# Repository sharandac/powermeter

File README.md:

<p align="center">

&nbsp;

&nbsp;

</p>
<hr/>

# powermeter

A not so simple but very flexible smart meter based on ESP32. It supports MQTT, live monitoring via web interface, IO ports ( can be switched depending on measured values ), a simple OLED driver for simple value reports, editable opcode sequences per channel and group management. And the best is: everything can also be set via the web interface and has immediate effect and invites to play to improve the understanding of AC voltage/current or DC voltage/current.<br>
<h3 style="color:#00ff00">Note: From version 2022110101 a complete reconfiguration is required.</h3>
<h3 style="color:#ff0000">Danger: Working with 110V or 230V is dangerous!</h3>

# install

Clone this repository and open it with platformIO. Remember, the SPIFF must also be flashed. On a terminal in vscode you can do it with
```bash
pio run -t uploadfs
pio run -t upload
```

After that, take a look at your monitorport ...

```text
Read config from SPIFFS
scan for SSID "" ... not found
starting Wifi-AP with SSID "powermeter_aadee0"
AP IP address: 192.168.4.1
Start Main Task on Core: 1
Start NTP Task on Core: 1
Start Measurement Task on Core: 0
Start MQTT-Client on Core: 1
Start Webserver on Core: 1
NTP-client: renew time
Start OTA Task on Core: 1
Failed to obtain time
NTP-client: Thursday, January 01 1970 01:00:07
```
When the output look like this, congratulation!

After the first start an access point will be opened with an unique name like
```bash
powermeter_XXXXX
```
and an not so unique password
```bash
powermeter
```
After that you can configure the powermeter under the following IP-address with your favorite webbrowser
```bash
http://192.168.4.1 or powermeter_xxxxxx.local
```
# how it works

At any time, all 6 adc channel are read in simultaneously regardless of the settings. Afterwards, these 6 ADC channels are distributed to 13 virtual channels with the help of editable microopcodes, each sample has a maximum of 10 opcodes available for real-time calculations (mixing, sum calculation, reactive power and so on). These 13 virtual channels can then be combined into a maximum of 6 output groups. For more information about how AC current or three-phase current and power calculations works, [read here](https://en.wikipedia.org/wiki/Alternating_current) and [here](https://en.wikipedia.org/wiki/Three-phase_electric_power)

# sensor hardware

## Sensors
SCT013-000 current sensor (~100A)<br>

ZMPT101B voltage sensor (~250V)<br>

ACS712 current sensor 5A, 20A and 30A<br>

simple voltage divider<br>

For ratio calculation see inline documentation via webinterface.

## Display hardware
Uncomment in "**display.cpp**" the line of the display you want to use<br>
```c
//#include <Adafruit_SSD1306.h>
//#include  <Adafruit_SH110X.h>
```

# Interface

## live view

## round trip

# contributors

Every Contribution to this repository is highly welcome! Don't fear to create pull requests which enhance or fix the project, you are going to help everybody.
<p>
If you want to donate to the author then you can buy me a coffee.
<br/><br/>

</p>

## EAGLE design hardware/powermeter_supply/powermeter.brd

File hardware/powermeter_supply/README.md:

# powermeter with supply

Here is the simplest standalone powermeter with supply you can build with current and voltage measurement.

## eagle files

[schematic](powermeter.sch)<br>
[board](powermeter.brd)

## bill of material

1 x 150x100x1mm 35µm FR4 [amazon](https://amzn.eu/d/hufknsN)<br>
esp32 D1 mini [amazon](https://amzn.eu/d/gZaocqF)<br>
ZMPT101 [amazon](https://amzn.eu/d/3shv3Ax)<br>
SCT-013-000 [amazon](https://amzn.eu/d/5wpwDs4)<br>
AC-05-03 ( 110-250V/AC -> 5V/DC ) [amazon](https://amzn.eu/d/ckoURve)<br>
3.5mm jack [amazon](https://amzn.eu/d/a7YUG0G)<br>
MSTBA2 connector [amazon](https://amzn.eu/d/0bCERTn)<br>
2 x 10k resistor<br>
1 x 62R resistor<br>
1 x 1M resistor<br>
1 x 2M resistor<br>
1 x 47µF cap<br>

## gcode

The G-code files are intended for Chilipeppr with a CNC3018 and contain everything. Engraving, drilling and cutting. There are two files. A normal one, where you should have your own gcode for tool change and length measurement and one with the appropriate gcode that also contains the length measurement. The reference point is X=0 and Y=0.

A backlash-free Z-axis is very important for accurate engraving of the tracks and cutting out!

The following tools are required:

0.1mm milling bit<br>
0.6mm drill bit<br>
0.9mm drill bit<br>
1.2mm drill bit<br>
1.3mm drill bit<br>
1.4mm drill bit<br>
2.0mm end mill<br>

Drag and drop the preferred gcode file into Chilipeppr. Autoleveling is a must. And then just press play. For the tool change, the program is paused at the appropriate position (M6).

If everything has gone well, you are rewarded with a finished board without any post-processing and is ready to soldering.

## config

After soldering and software installtion (wifi,mqtt and so on) you can copy the content from config/measure.json to your powermeter. From here you can tweake the ratio settings for precise measuring via web interface under "channel settings".

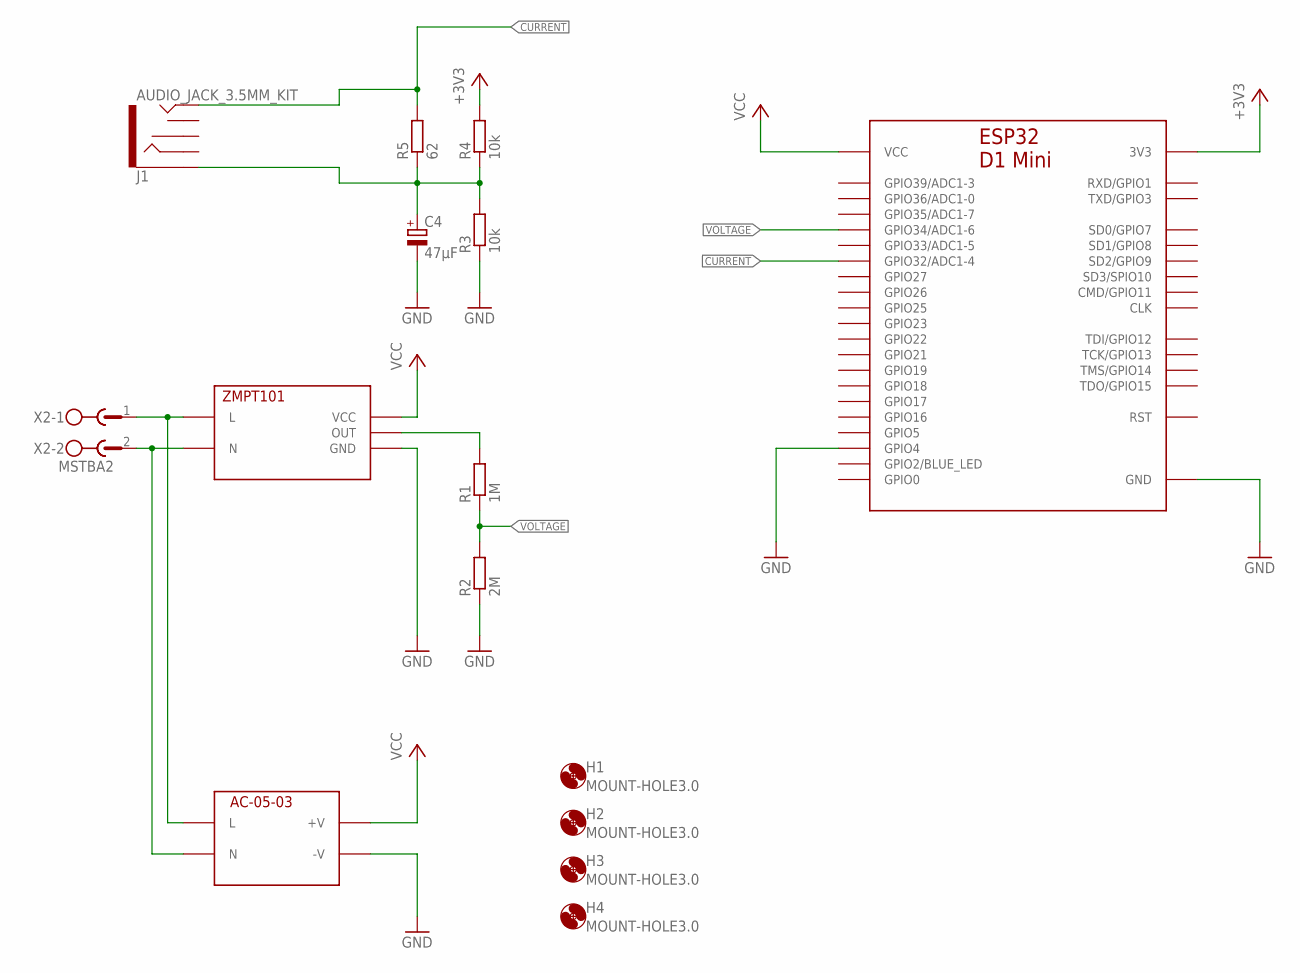
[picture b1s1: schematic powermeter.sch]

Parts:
C4: 47µF; E2,5-5
H1, H2, H3, H4: MOUNT-HOLE3.0; 3,0
J1: AUDIO_JACK_3.5MM_KIT; AUDIO-JACK-KIT
R1: 1M; 0204/7
R2: 2M; 0204/7
R3, R4: 10k; 0204/7
R5: 62; 0204/7
U1: ESP32D1MINI
U$1: ZMPT101
U$2: AC-05-03
X2: MSTBA2

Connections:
+3V3: R4.2, U1.3V3
CURRENT: J1.TIP, R5.2, U1.IO32 (GPIO32/ADC1-4)
GND: C4.-, R2.1, R3.1, U1.GND1 (GND), U1.GND2 (GND), U1.GND3 (GND), U1.IO4 (GPIO4), U$1.P$3 (GND), U$1.P$4 (GND), U$2.-V
unnamed: R1.2, U$1.OUT
unnamed: U$1.L, U$2.L, X2.1
unnamed: C4.+, J1.SLEEVE, R3.2, R4.1, R5.1
unnamed: U$1.N, U$2.N, X2.2
VCC: U1.VCC, U$1.VCC, U$2.+V
VOLTAGE: R1.1, R2.2, U1.IO34 (GPIO34/ADC1-6)

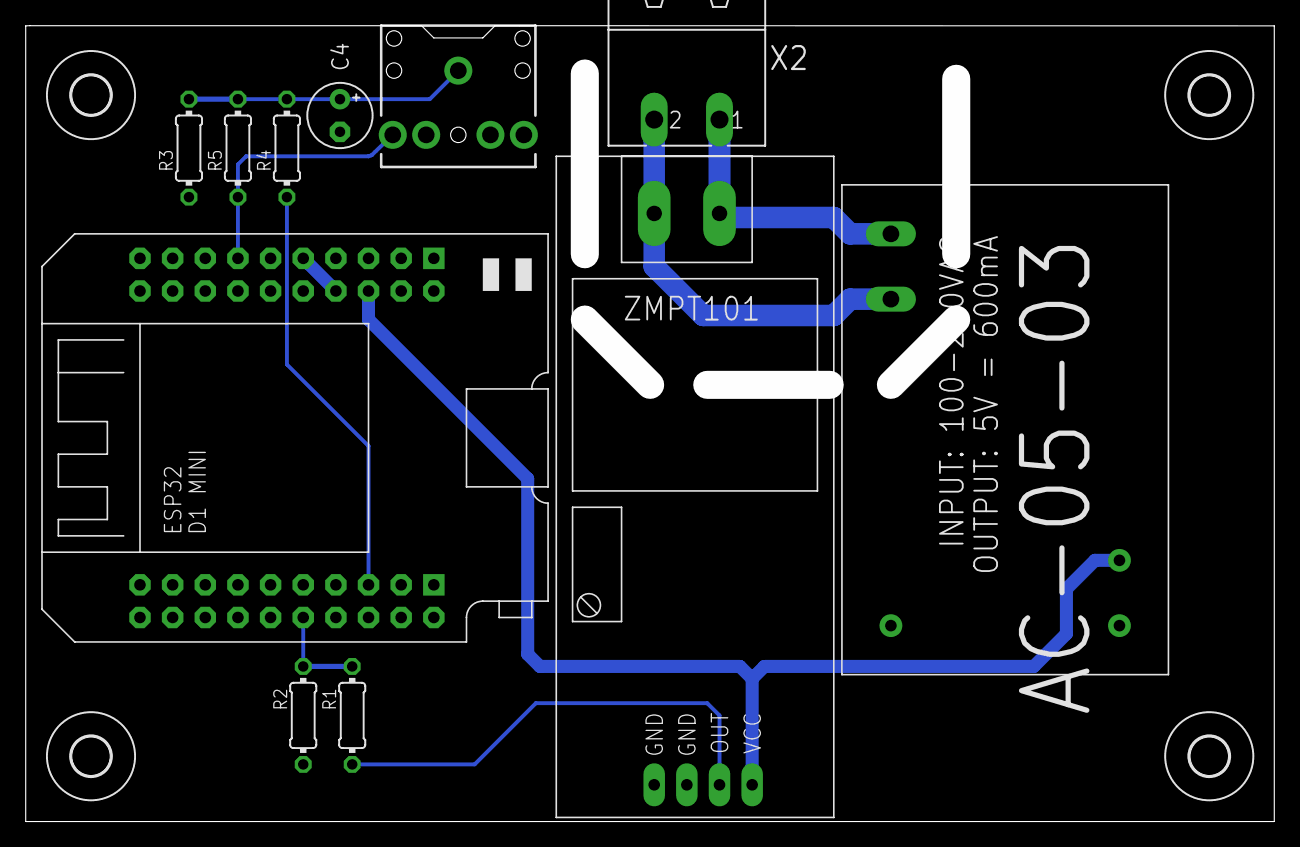
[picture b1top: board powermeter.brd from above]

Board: 2 copper layers, 95.0 x 59.7 mm, 15 parts (0 on the bottom side), 9 nets.

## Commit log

2019-07-11 first release
2019-07-13 some performace and stability improvement
2019-07-30 improve web interface performance
2019-11-09 some changes
2019-11-10 add some screenshoot
2019-11-11 some issue with AsyncTCP, fix to version 1.0.3
2020-05-27 switch to the internal i2s interface of the built-in adc
2020-06-09 port to i2s interface, 3channel support
2020-06-09 update documentation
2020-06-09 add options for 50/60Hz AC voltage frequency. some css improvements.
2020-06-10 add hardware dokumentation
2020-06-13 update schematic
2020-06-13 add current information over mqtt for each channel
2020-06-16 fix wlan issue and security fixes
2020-06-16 fix data types, send json msg to mqtt
2020-06-16 update docu
2020-06-18 remove arduino.h
2020-06-18 clean up local scopes
2020-06-20 abtract channels
2020-06-20 code style and documentation
2020-06-20 add phaseshift option
2020-06-20 some code abtraction
2020-06-22 add virtual channels and channel math
2020-06-23 up to 6 channels and some memory improvement
2020-06-25 read for current and voltage measurement
2020-06-26 optical changes and doku
2020-06-26 update signalpath
2020-09-09 update mqtt json message format
2021-03-02 fix samplefreq correction setup
2021-03-19 add precise network frequency (phaseshift method)
2021-08-12 add current offset settings
2021-08-12 update spiffs image
2021-08-20 update binary config to json
2021-08-22 update onDefault handling
2021-08-24 add channel opcodeseq option in json config
2021-08-27 add opcode sequence web editor
2021-08-29 add microcode editor and update html files
2021-08-29 update spiffs
2021-08-29 update htm files
2021-08-30 update docu, html and binary files
2021-08-30 update version
2022-04-16 Create Sjenica1
    Authorized mit meine Account Sjenica1 github.com reufrujevic750@gmail.com
2022-04-20 documentation and refactoring
2022-04-23 add config over mqtt
2022-08-01 fix bufferoverflow and esp32 ide version
2022-08-18 update signalpath graph
2022-08-25 some small fixes and docu update
2022-08-26 update binary files
2022-09-29 some major updates
2022-09-29 update imag path
2022-10-01 some fixes and updates
2022-10-01 fix typo
2022-10-03 some updates
2022-10-03 cleanup and documentation
2022-10-05 change frequency measurement channel
2022-10-06 some fixing
2022-10-19 fix some bugs and add hardware
2022-10-25 some small updates
2022-10-27 update some things
2022-10-31 Update finalisation

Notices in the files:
parts and their libraries:
SparkFun-Connectors: Licensing: Creative Commons ShareAlike 4.0 International - https://creativecommons.org/licenses/by-sa/4.0
